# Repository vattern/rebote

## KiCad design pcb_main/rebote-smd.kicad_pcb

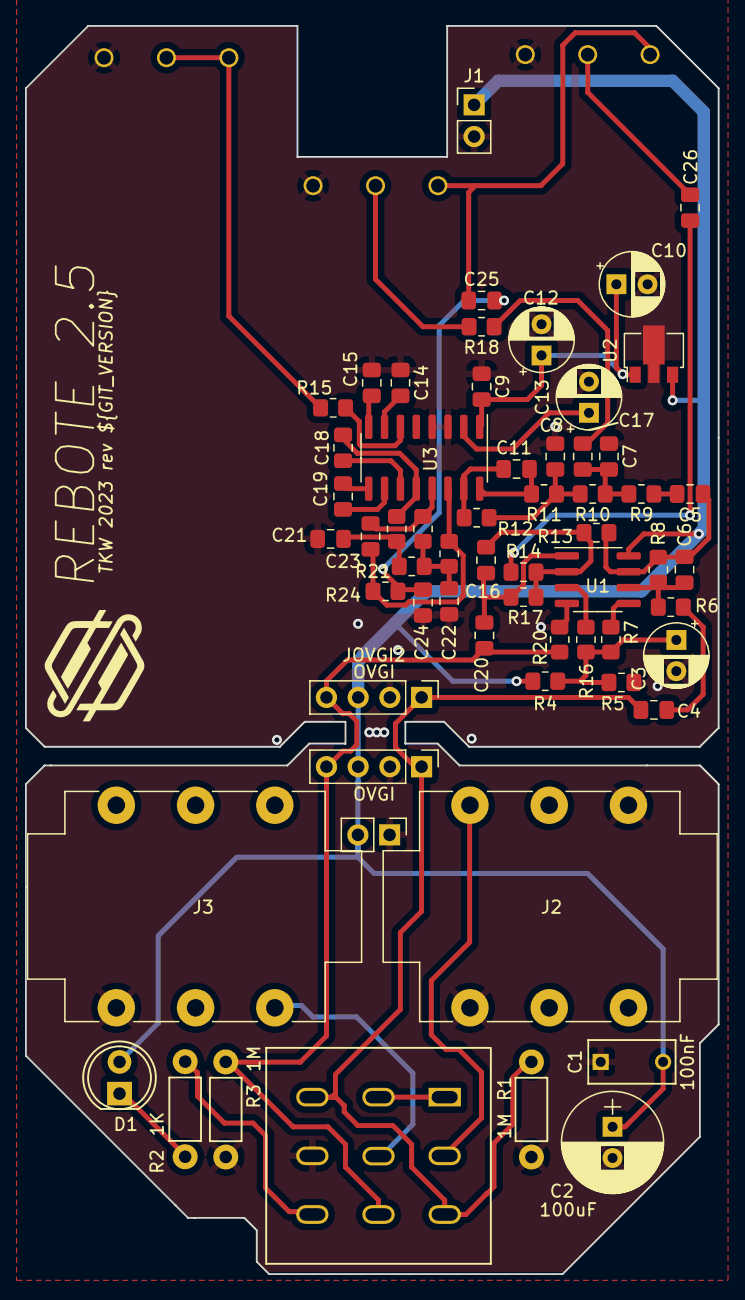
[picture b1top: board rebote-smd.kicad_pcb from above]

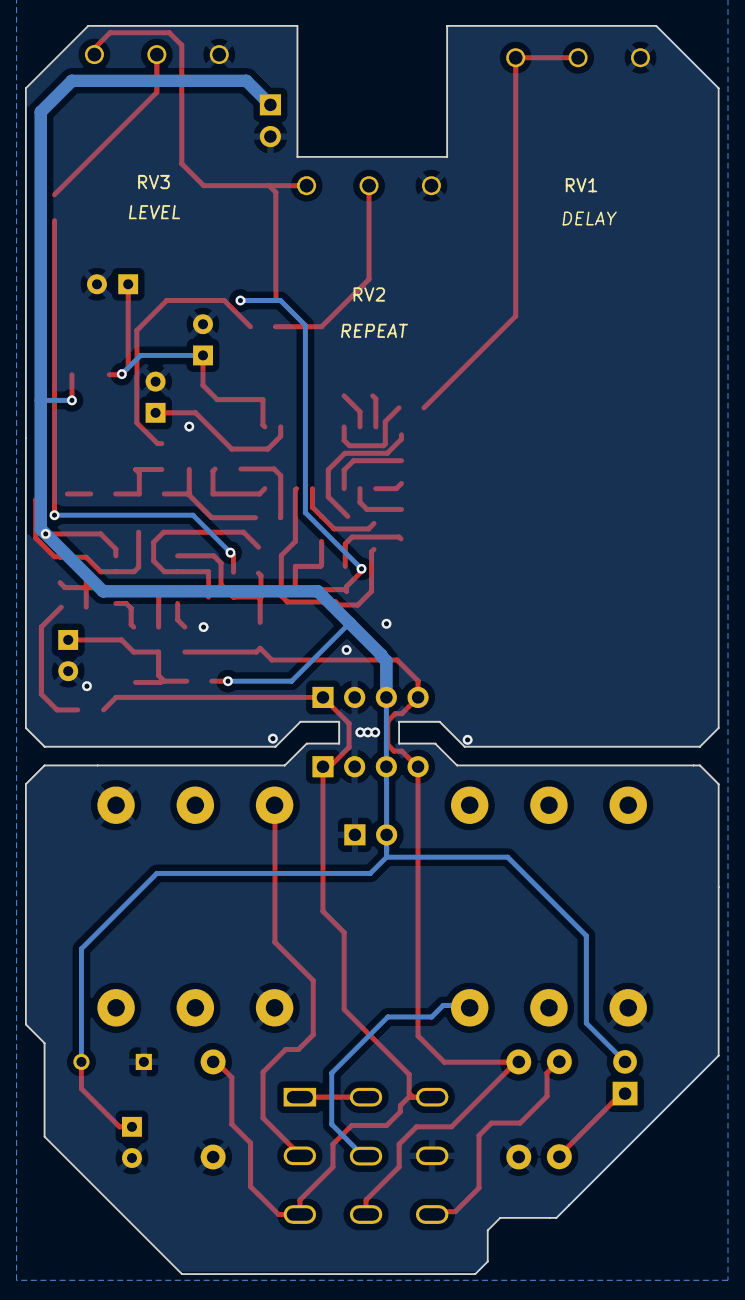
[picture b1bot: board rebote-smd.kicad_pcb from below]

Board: 2 copper layers, 55.5 x 100.0 mm, 65 parts (3 on the bottom side), 42 nets.

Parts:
C1: 100nF; C_Rect_L7_W3.5_P5
C2: 100uF; CP_Radial_D8.0mm_P2.50mm
C3, C10, C12, C13: 47uF; CP_Radial_D5.0mm_P2.50mm
C4: 8n2; C_0805_2012Metric_Pad1.18x1.45mm_HandSolder
C5, C20, C25, C26: 1uF; C_0805_2012Metric_Pad1.18x1.45mm_HandSolder
C6: 5pF; C_0805_2012Metric_Pad1.18x1.45mm_HandSolder
C7: 27nF; C_0805_2012Metric_Pad1.18x1.45mm_HandSolder
C8, C21, C22: 10nF; C_0805_2012Metric_Pad1.18x1.45mm_HandSolder
C9, C14, C15, C17, C24: 100nF; C_0805_2012Metric_Pad1.18x1.45mm_HandSolder
C11: 560pF; C_0805_2012Metric_Pad1.18x1.45mm_HandSolder
C16: 51pF; C_0805_2012Metric_Pad1.18x1.45mm_HandSolder
C18, C19: 82nF; C_0805_2012Metric_Pad1.18x1.45mm_HandSolder
C23: 1nF; C_0805_2012Metric_Pad1.18x1.45mm_HandSolder
D1: LED; LED-5MM
J1, J4: V+ GND; PinHeader_1x02_P2.54mm_Vertical
J2, J3: NMJ6HCD2; Jack_6.35mm_Neutrik_NMJ6HCD2_Horizontal
JOVGI1, JOVGI2: OVGI; Pin_Header_Straight_1x04_Pitch2.54mm
N1: Housing; 1590B
R1, R3: 1M; Resistor_Horizontal_RM7mm
R2: 1K; Resistor_Horizontal_RM7mm
R4, R5, R9, R10, R11, R19, R21, R22: 12K; R_0805_2012Metric_Pad1.20x1.40mm_HandSolder
R6, R7, R8: 510K; R_0805_2012Metric_Pad1.20x1.40mm_HandSolder
R12: 47K; R_0805_2012Metric_Pad1.20x1.40mm_HandSolder
R13, R17, R23: 24K; R_0805_2012Metric_Pad1.20x1.40mm_HandSolder
R14: 33K; R_0805_2012Metric_Pad1.20x1.40mm_HandSolder
R15, R16: 1k; R_0805_2012Metric_Pad1.20x1.40mm_HandSolder
R18: 15K; R_0805_2012Metric_Pad1.20x1.40mm_HandSolder
R20: 100K; R_0805_2012Metric_Pad1.20x1.40mm_HandSolder
R24: 2k7; R_0805_2012Metric_Pad1.20x1.40mm_HandSolder
RV1: 50KB; Potentiometer_ALPHA_RV16106N
RV2: 25KB; Potentiometer_ALPHA_RV16106N
RV3: 100KB; Potentiometer_ALPHA_RV16106N
SW1: SW_3PDT; 3PDT-Footswitch
U1: TL072; SOIC-8_3.9x4.9mm_P1.27mm
U2: L78L05_SOT89; SOT-89-3
U3: PT2399; SOIC-16_3.9x9.9mm_P1.27mm

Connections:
+5V: C9.2, C10.1, C12.1, U2.1 (OUT), U3.1 (VCC)
+9V: C1.2, C2.1, D1.2 (A), J1.1, J4.2, JOVGI1.3, JOVGI2.3, R4.1, U1.8 (V+), U2.3 (IN)
AI: C5.1, C6.2, R8.2, R13.1, U1.7
DELAY_OUT: C18.2, R19.1, U3.12 (OP2-OUT)
GND: C1.1, C2.2, C3.2, C7.1, C8.1, C9.1, C10.2, C12.2, C13.2, C14.1, C15.1, C21.1, C22.1, C24.1, J1.2, J2.S, J2.TN, J3.S, J4.1, JOVGI1.2, JOVGI2.2, R1.2, R3.2, R5.2, R20.1, RV1.1, RV2.1, RV3.1, SW1.6 (B), U1.4 (V-), U2.2 (GND), U3.3 (AGND), U3.4 (DGND)
I: C4.1, JOVGI1.1, JOVGI2.1, R1.1, SW1.3 (A), SW1.7 (C)
LPF1-IN: C11.1, R11.2, U3.16 (LPF1-IN)
LPF1-OUT: C11.2, R12.2, U3.15 (LPF1-OUT)
LPF2-IN: C23.1, R22.2, U3.13 (LPF2-IN)
LPF2-OUT: C23.2, R23.2, R24.1, U3.14 (LPF2-OUT)
unnamed: C4.2, R6.1
unnamed: C5.2, R9.1
unnamed: C8.2, R10.2, R11.1, R12.1
unnamed: C16.2, C20.1, R17.2, U1.1
unnamed: C7.2, C17.1, R9.2, R10.1
unnamed: C17.2, R18.1
unnamed: C21.2, R19.2, R21.1
unnamed: C22.2, R21.2, R22.1, R23.1
unnamed: C24.2, C25.1, R24.2
unnamed: C25.2, RV2.3, RV3.3
unnamed: C26.1, RV3.2
unnamed: C26.2, R14.1
unnamed: D1.1 (K), R2.1
unnamed: R15.2, RV1.2, RV1.3
unnamed: R18.2, RV2.2
unnamed: SW1.1 (A), SW1.2 (A)
unnamed: J2.T, SW1.4 (B)
unnamed: J3.T, SW1.5 (B)
unnamed: R2.2, SW1.9 (C)
unnamed: R16.2, U1.3 (+)
unnamed: C16.1, R13.2, R14.2, R17.1, U1.2 (-)
unnamed: R7.2, U1.5 (+)
unnamed: C6.1, R6.2, R8.1, U1.6 (-)
unnamed: C15.2, U3.8 (CC0)
unnamed: C14.2, U3.7 (CC1)
unnamed: C19.2, U3.10 (OP1-IN)
unnamed: C19.1, U3.9 (OP1-OUT)
unnamed: C18.1, U3.11 (OP2-IN)
unnamed: C13.1, U3.2 (REF)
unnamed: R15.1, U3.6 (VCO)
O: C20.2, JOVGI1.4, JOVGI2.4, R3.1, R20.2, SW1.8 (C)
VD: C3.1, R4.2, R5.1, R7.1, R16.1

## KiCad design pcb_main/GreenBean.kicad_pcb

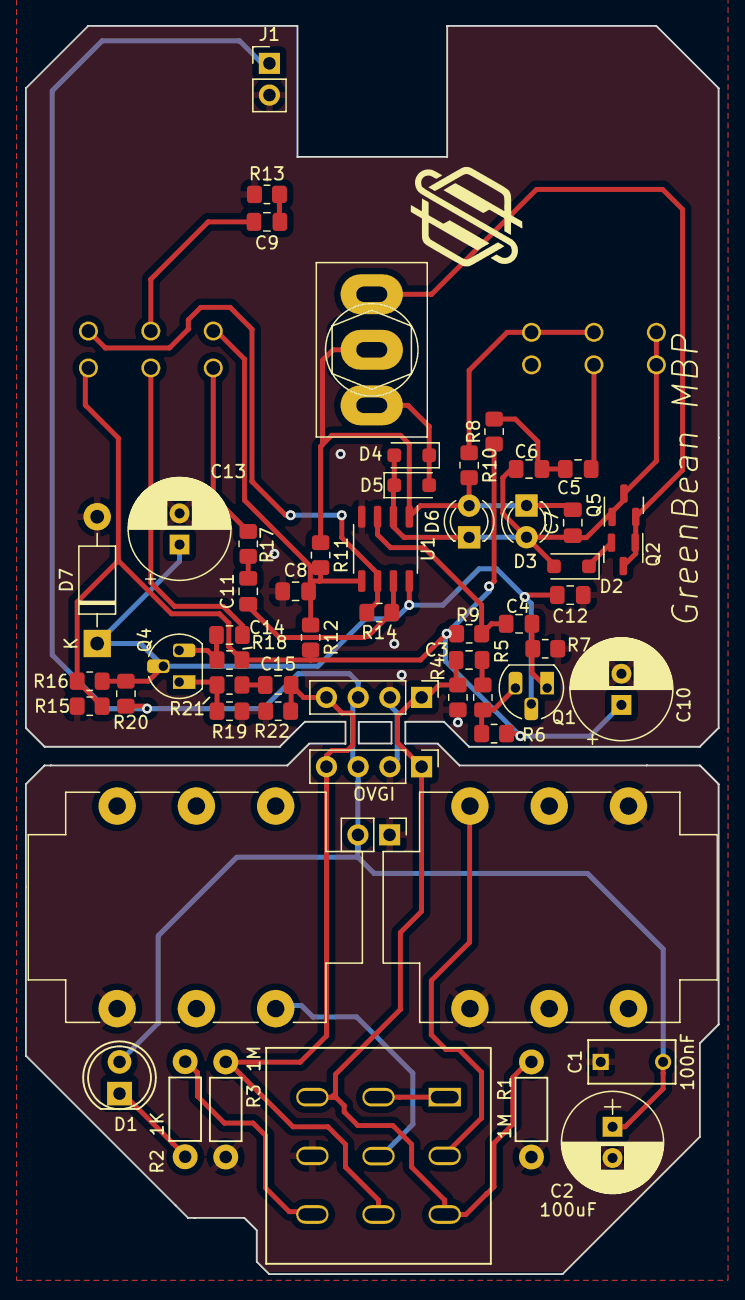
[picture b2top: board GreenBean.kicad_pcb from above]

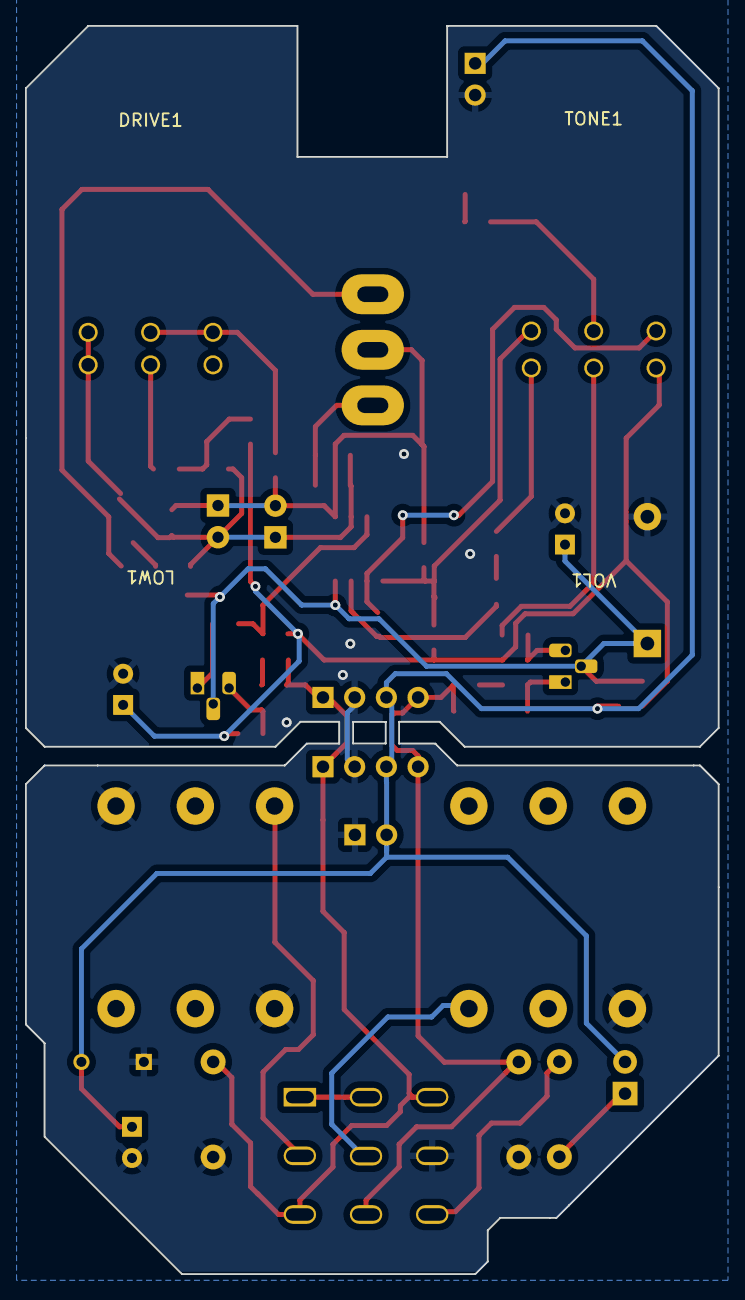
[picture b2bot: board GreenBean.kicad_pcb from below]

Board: 2 copper layers, 55.5 x 100.0 mm, 62 parts (4 on the bottom side), 34 nets.

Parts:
C1: 100nF; C_Rect_L7_W3.5_P5
C2, C13: 100uF; CP_Radial_D8.0mm_P2.50mm
C3: 20n; C_0805_2012Metric_Pad1.18x1.45mm_HandSolder
C4, C11, C15: 1u; C_0805_2012Metric_Pad1.18x1.45mm_HandSolder
C5: 150n; C_0805_2012Metric_Pad1.18x1.45mm_HandSolder
C6: 47n; C_0805_2012Metric_Pad1.18x1.45mm_HandSolder
C7: 51p; C_0805_2012Metric_Pad1.18x1.45mm_HandSolder
C8, C9, C12: 220n; C_0805_2012Metric_Pad1.18x1.45mm_HandSolder
C10: 10uF; CP_Radial_D8.0mm_P2.50mm
C14: 100n; C_0805_2012Metric_Pad1.18x1.45mm_HandSolder
D1: LED; LED-5MM
D2: BAT41; D_SOD-123F
D3, D6: LED; LED_D3.0mm
D4, D5: 1N914; D_SOD-123F
D7: 1N4001; D_DO-41_SOD81_P10.16mm_Horizontal
DRIVE1: 500KA; Potentiometer_ALPHA_RV16106N
J1, J4: V+ GND; PinHeader_1x02_P2.54mm_Vertical
J2, J3: NMJ6HCD2; Jack_6.35mm_Neutrik_NMJ6HCD2_Horizontal
JOVGI1, JOVGI2: OVGI; Pin_Header_Straight_1x04_Pitch2.54mm
LOW1: 20KB; Potentiometer_ALPHA_RV16106N
N1: Housing; 1590B
Q1, Q4: 2SC1815; TO-92L_HandSolder
Q2, Q5: 2N7002; SOT-23
R1, R3: 1M; Resistor_Horizontal_RM7mm
R2: 1K; Resistor_Horizontal_RM7mm
R4: 1M; R_0805_2012Metric_Pad1.20x1.40mm_HandSolder
R5, R11, R14, R17: 1k; R_0805_2012Metric_Pad1.20x1.40mm_HandSolder
R6, R18: 510k; R_0805_2012Metric_Pad1.20x1.40mm_HandSolder
R7, R9, R12, R15, R16, R19, R22: 10k; R_0805_2012Metric_Pad1.20x1.40mm_HandSolder
R8: 4k7; R_0805_2012Metric_Pad1.20x1.40mm_HandSolder
R10: 51k; R_0805_2012Metric_Pad1.20x1.40mm_HandSolder
R13: 220R; R_0805_2012Metric_Pad1.20x1.40mm_HandSolder
R20: 47R; R_0805_2012Metric_Pad1.20x1.40mm_HandSolder
R21: 100R; R_0805_2012Metric_Pad1.20x1.40mm_HandSolder
SW1: SW_3PDT; 3PDT-Footswitch
SW2: SW_SPDT; SW_Toggle_Blue_wSlots
TONE1: 20KB; Potentiometer_ALPHA_RV16106N
U1: RC4558; SO-8_3.9x4.9mm_P1.27mm
VOL1: 100KB; Potentiometer_ALPHA_RV16106N

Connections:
+9V: C1.2, C2.1, D1.2 (A), J1.1, J4.2, JOVGI1.3, JOVGI2.3, R20.2
A: C6.2, C7.1, D2.2 (A), D3.2 (A), D4.2 (A), D5.1 (K), D6.1 (K), DRIVE1.1, LOW1.3, Q5.1 (G), Q5.3 (D), U1.2 (-)
B: C7.2, D3.1 (K), D6.2 (A), R10.2, R11.1, SW2.2, U1.1
GND: C1.1, C2.2, C8.1, C10.2, C12.1, C13.2, D7.2 (A), J1.2, J2.S, J2.TN, J3.S, J4.1, JOVGI1.2, JOVGI2.2, R1.2, R3.2, R4.1, R7.1, R13.1, R15.1, R19.1, R22.1, SW1.6 (B), U1.4 (V-)
I: C3.1, JOVGI1.1, JOVGI2.1, R1.1, R4.2, SW1.3 (A), SW1.7 (C)
unnamed: C3.2, R5.2
unnamed: C5.1, C6.1, R8.2
unnamed: C5.2, LOW1.2
unnamed: C9.1, R13.2
unnamed: C9.2, TONE1.2
unnamed: C11.1, R14.2, U1.7
unnamed: C11.2, R17.1
unnamed: C14.1, VOL1.2
unnamed: C15.1, R21.2
unnamed: D1.1 (K), R2.1
unnamed: D2.1 (K), Q2.2 (S)
unnamed: D4.1 (K), D5.2 (A), SW2.1
unnamed: DRIVE1.2, DRIVE1.3, R10.1
unnamed: Q1.3 (B), R5.1, R6.1
unnamed: C4.1, Q1.1 (E), R7.2
unnamed: Q2.1 (G), Q2.3 (D), Q5.2 (S), SW2.3
unnamed: C14.2, Q4.3 (B), R18.1
unnamed: Q4.1 (E), R19.2, R21.1
unnamed: R17.2, VOL1.3
unnamed: SW1.1 (A), SW1.2 (A)
unnamed: J2.T, SW1.4 (B)
unnamed: J3.T, SW1.5 (B)
unnamed: R2.2, SW1.9 (C)
unnamed: C4.2, R9.1, U1.3 (+)
unnamed: C8.2, R11.2, R12.1, TONE1.1, U1.5 (+)
unnamed: R14.1, TONE1.3, U1.6 (-)
O: C15.2, JOVGI1.4, JOVGI2.4, R3.1, R22.2, SW1.8 (C)
VB: C10.1, R6.2, R8.1, R9.2, R12.2, R15.2, R16.1, R18.2, VOL1.1
VC: C12.2, C13.1, D7.1 (K), Q1.2 (C), Q4.2 (C), R16.2, R20.1, U1.8 (V+)

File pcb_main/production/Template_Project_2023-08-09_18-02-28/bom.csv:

Designator,Footprint,Quantity,Value,LCSC Part #
C1,C_Rect_L7_W3.5_P5,1,100nF,
C10,CP_Radial_D8.0mm_P2.50mm,1,10uF,
"C11, C15, C4",0805,3,1u,
"C12, C8, C9",0805,3,220n,
"C13, C2",CP_Radial_D8.0mm_P2.50mm,2,100uF,
C14,0805,1,100n,
C3,0805,1,20n,
C5,0805,1,150n,
C6,0805,1,47n,
C7,0805,1,51p,
D1,LED-5MM,1,LED,
D2,D_SOD-123F,1,BAT41,
"D3, D6",LED_D3.0mm,2,LED,
"D4, D5",D_SOD-123F,2,1N914,
D7,D_DO-41_SOD81_P10.16mm_Horizontal,1,1N4001,
DRIVE1,Potentiometer_ALPHA_RV16106N,1,500KA,
"J1, J4",PinHeader_1x02_P2.54mm_Vertical,2,V+ GND,
"J2, J3",Jack_6.35mm_Neutrik_NMJ6HCD2_Horizontal,2,NMJ6HCD2,
"JOVGI1, JOVGI2",Pin_Header_Straight_1x04_Pitch2.54mm,2,OVGI,
"LOW1, TONE1",Potentiometer_ALPHA_RV16106N,2,20KB,
N1,1590B,1,Housing,
"Q1, Q4",TO-92L_HandSolder,2,2SC1815,
"Q2, Q5",SOT-23,2,2N7002,
"R1, R3",Resistor_Horizontal_RM7mm,2,1M,
R10,0805,1,51k,
"R11, R14, R17, R5",0805,4,1k,
"R12, R15, R16, R19, R22, R7, R9",0805,7,10k,
R13,0805,1,220R,
"R18, R6",0805,2,510k,
R2,Resistor_Horizontal_RM7mm,1,1K,
R20,0805,1,47R,
R21,0805,1,100R,
R4,0805,1,1M,
R8,0805,1,4k7,
SW1,3PDT-Footswitch,1,SW_3PDT,
SW2,SW_Toggle_Blue_wSlots,1,SW_SPDT,
U1,SO-8_3.9x4.9mm_P1.27mm,1,RC4558,
VOL1,Potentiometer_ALPHA_RV16106N,1,100KB,

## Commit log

2023-08-10 Updates to template
2023-08-10 Deploying to main from @ vattern/rebote@6df6b5871361c08d3a09418d04a5add66901d4e8 🚀
2023-08-10 update workflow
2023-08-10 Deploying to main from @ vattern/rebote@4d7baf261b45e5b9ec4b56d51d7bcefacfe4e841 🚀
2023-08-10 Deploying to main from @ vattern/rebote@61408f5c9c0158da34629f1a671ace3053866393 🚀
2023-08-10 Add git push
2023-08-10 Add changes
2023-08-10 Deploying to main from @ vattern/rebote@c3620852507b189bb969dee9434ed4e47aee84b6 🚀
2023-08-10 Add version tag
2023-08-10 Poke workflow
2023-08-10 Deploying to main from @ vattern/rebote@82885d3c062bac5c756875c2e98ab2af4ec8d984 🚀
2023-08-10 Tweak deploy checkout
2023-08-10 Deploying to main from @ vattern/rebote@cfbd7d0e9a3340e9276a4ae94dfe695da83264e6 🚀
2023-08-10 Poke version number in pcb file
2023-08-10 Deploying to main from @ vattern/rebote@dedd87cc4f30aa74d470bbaad9a0601b0c75b75a 🚀
2023-08-10 Update the workflow
2023-08-10 Deploying to main from @ vattern/rebote@1a68f10a6b263f328bbfc9e0ac1533878929f32d 🚀
2023-08-10 Update the settings to export blender
2023-08-10 Deploying to main from @ vattern/rebote@ec7f0b099f100d734cf029f8513aac406e1b986f 🚀
2023-08-10 Remove un needed dwg. Move value in sch
2023-08-10 Add changes [ci skip]
2023-08-10 Deploying to main from @ vattern/rebote@3383320137013611349b0625d1877040ce42659b 🚀
2023-08-10 File cleanup
2023-08-10 Deploying to main from @ vattern/rebote@68b1c407168fae85a5e36206cf402d89d7a8a9e6 🚀
2023-08-10 do a pull
2023-08-10 Deploying to main from @ vattern/rebote@c86c1c599171f6f04c3675a5e5bf3eda7962da2f 🚀
